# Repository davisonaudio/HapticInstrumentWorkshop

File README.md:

# HaptiCoupler System

This repository contaisn the design files and firmware for the HaptiCoupler system.
It also contains information for the Haptic instrument study that used the HaptiCoupler system to explore digital musical instrument designs.

More information about the system can be found in the Wiki tab of this repo.

The HaptiCoupler is a device that enables simultaneous tactile sensing and haptic feedback through a signle voice coil transducer.

This is achieved by actuating the voice coil with a voltage and sensing with current, along with some DSP running on the Teensy 4.0 to cancel the actuation signal from the sensing signal.

It is designed primarily for use with audio-driven digital resonator instruments, though can be used for other purposes.

# HapticInstrumentWorkshop
Information for the self-sensing vibrotactile haptic instrument design project. Part of the Augmented Instruments Lab at Imperial College London

For more information on using the kit and detailed documentation, visit the [wiki](https://github.com/davisonaudio/HapticInstrumentWorkshop/wiki).

Access the web control panel [here](https://davisonaudio.github.io/HapticInstrumentWorkshop/) for logging information and parameter adjustment.

# Kit Contents

- 1x Teensy 4.0 Microcontroller development board with headers
- 1x custom amplifier PCB (using MAX98789 amplifier)
- 1x Dayton Audio EX32VBDS-4 Voice Coil Transducer
- 1x 9V DC 5.1mm barrel jack power supply (centre-positive)
- 1x USB A to micro USB cable

# Getting Started
The Teensy 4.0 will come preloaded with the required firmware and mounted with its headers onto the top of the amplifier board. 

# Cloning the repo
To get a local copy of this repository (for editing the firmware or hardware files included), run the following command:
> git clone --recurse-submodules https://github.com/davisonaudio/HapticInstrumentWorkshop.git

This will clone the main repo as well as the audio-utils submodule within the firmware folder.

# Hacking the Hardware

It is unlikely that the PCB is something that we be modified as part of this study. For those with sufficient electronics knowledge, however, the design files (schematic and PCB PDFs along with KiCAD files) can be found in the hardware folder of this repo.

# Hacking the Example Software

# Hacking the Firmware
For advanced users, the firmware running on the Teensy can be modified and recompiled. All of the required files are within the firmware folder of this repo.

The firmware is developed for the Teensy using [PlatformIO](https://platformio.org). This provides more flexibility than using the Arduino IDE (as is often used with Teensy and similar boards), but still allows use of the Teensy system's wide array of useful C++ libraries. It also avoids the increased complexities of utilising a proper embedded development environment (such as NXP's MCUXpresso for the Teensy 4.0's NXP RT1060 microcontroller).

Visual Studio Code is required for PlatformIO development. For further details of development environment setup please refer to the wiki.

# Publications
For more information on related research output of this project, please refer to the below publications:

- M. Davison, C. J. Webb, M. Ducceschi and A. P. McPherson. A self-sensing haptic actuator for tactile interaction with physical modelling synthesis. *Proc. International Conference on New Interfaces for Musical Expression (NIME)*, Utrecht, Netherlands. 2024. [PDF](http://instrumentslab.org/data/andrew/davison_nime2024.pdf)

- M. Davison and A. P. McPherson. A self-sensing vibrotactile transducer for bidirectional interaction. *Proc. Eurohaptics* (work in progress), Lille, France. 2024. [PDF](http://instrumentslab.org/data/andrew/davison_eurohaptics2024.pdf)

# Contributors
This project is developed and maintained by Matt Davison. Massive thank you also to the additional contributors who helped this project happen:

- Anna Silver - CAD design of 3D printed elements
- David Gong - Initial PCB design and firmware bring-up of the amplifier board
- Prof. Andrew McPherson - Supervision and guidance throughout

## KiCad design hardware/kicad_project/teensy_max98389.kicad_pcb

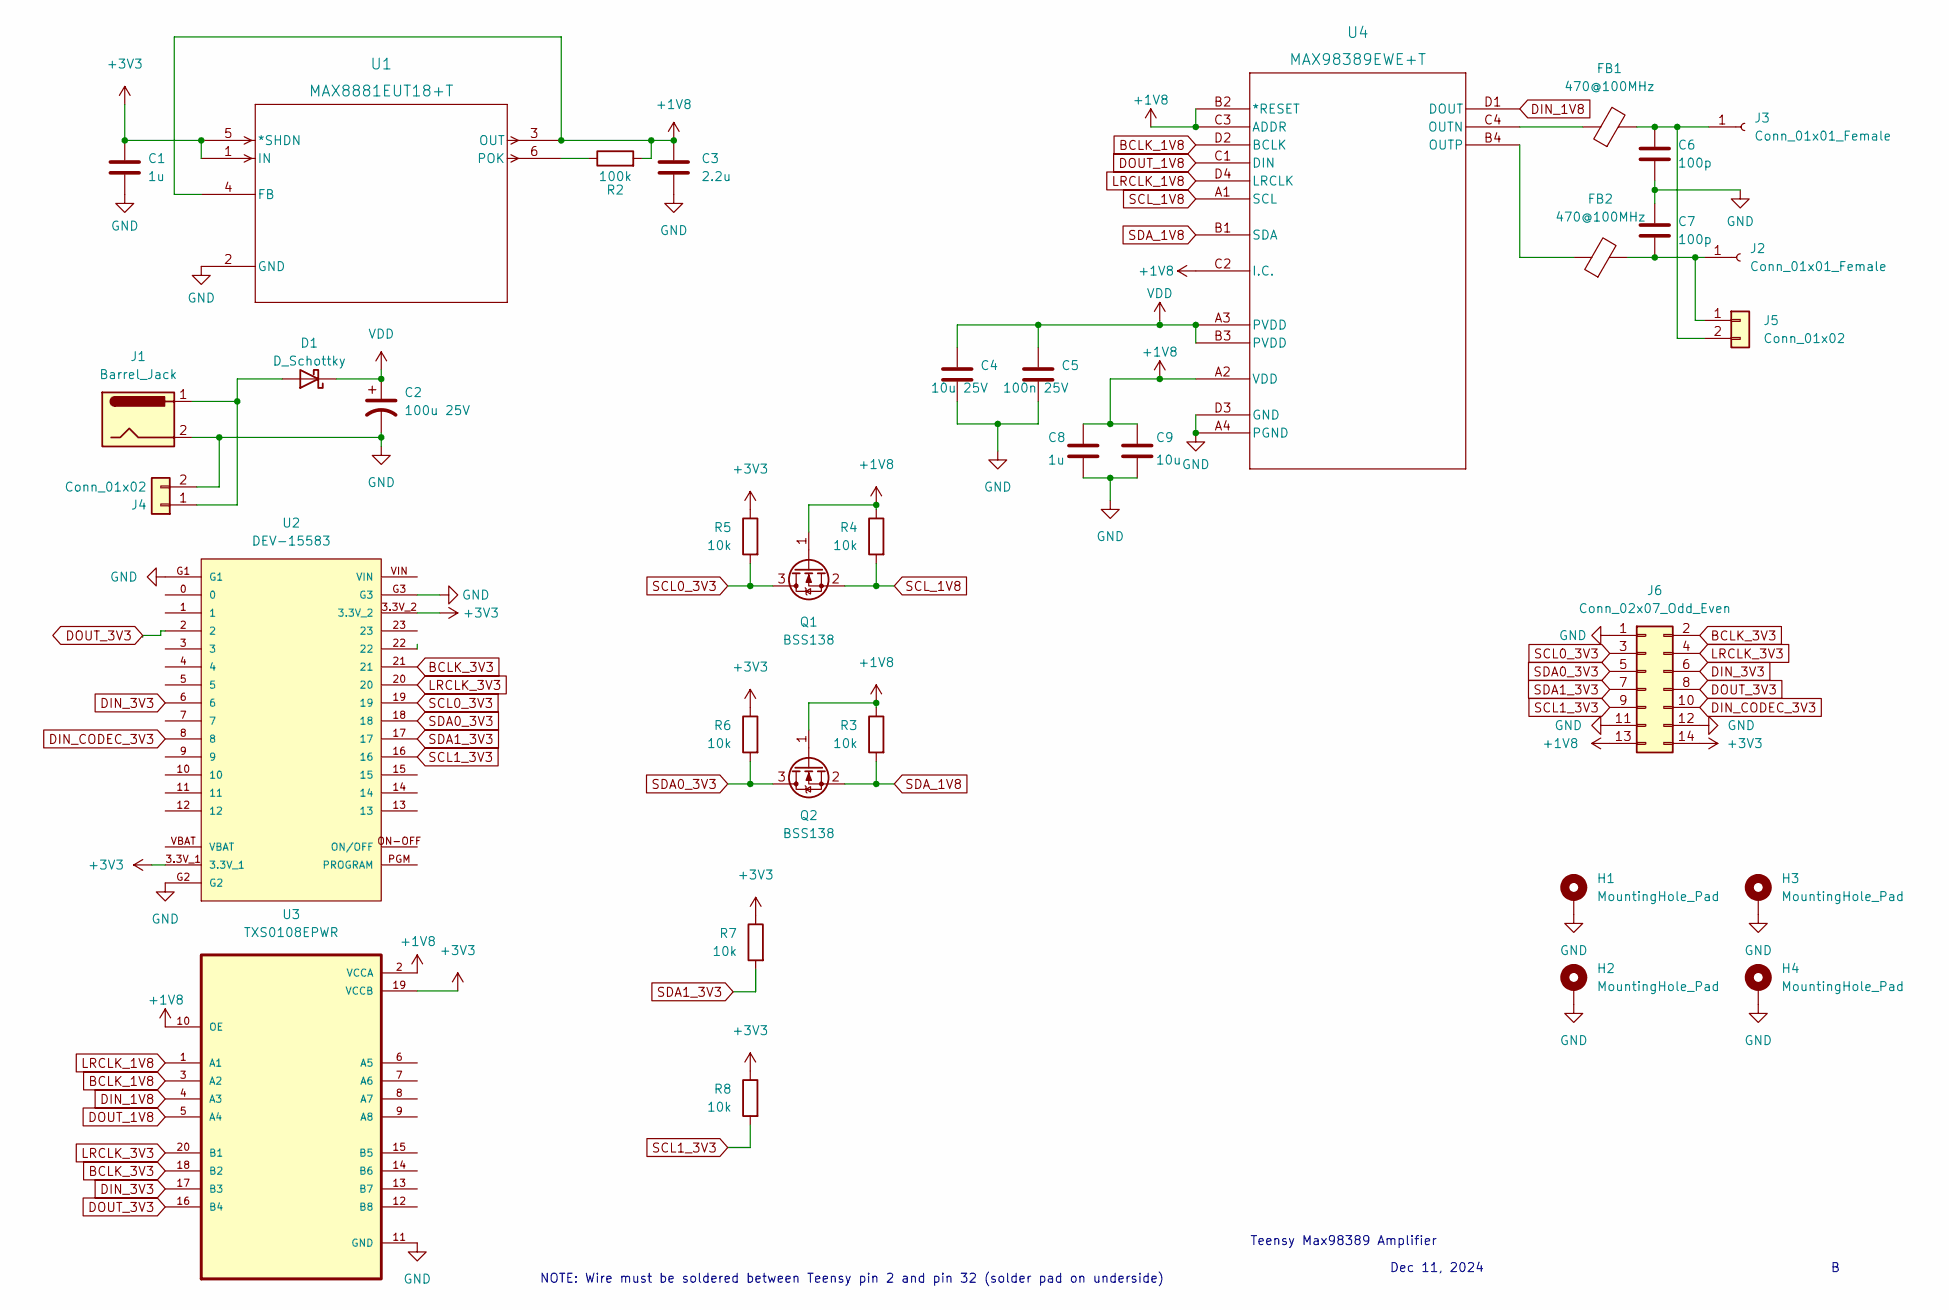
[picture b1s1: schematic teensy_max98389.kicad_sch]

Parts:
C1, C8: 1u; C_0603_1608Metric
C2: 100u 25V; CP_Radial_D6.3mm_P2.50mm
C3: 2.2u; C_0603_1608Metric
C4: 10u 25V; C_0603_1608Metric
C5: 100n 25V; C_0603_1608Metric
C6, C7: 100p; C_0603_1608Metric
C9: 10u; C_0603_1608Metric
D1: D_Schottky; D_0603_1608Metric
FB1, FB2: 470@100MHz; L_0805_2012Metric
H1, H2, H3, H4: MountingHole_Pad; MountingHole_3.2mm_M3_DIN965_Pad_TopBottom
J1: Barrel_Jack; BarrelJack_Kycon_KLDX-0202-xC_Horizontal
J2, J3: Conn_01x01_Female; MountingHole_6.4mm_M6_DIN965_Pad
J4, J5: Conn_01x02; Molex_KK-254_AE-6410-02A_1x02_P2.54mm_Vertical
J6: Conn_02x07_Odd_Even; PinHeader_2x07_P2.54mm_Vertical
Q1, Q2: BSS138; SOT-23
R2: 100k; R_0603_1608Metric
R3, R4, R5, R6, R7, R8: 10k; R_0603_1608Metric
U1: MAX8881EUT18+T; 21-0058I_MXM
U2: DEV-15583; MODULE_DEV-15583
U3: TXS0108EPWR; SOP65P640X120-20N
U4: MAX98389EWE+T; 21-100636_ADI

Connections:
+1V8: C3.1, C8.1, C9.1, J6.13, Q1.1 (G), Q2.1 (G), R2.2, R3.1, R4.1, U1.3 (OUT), U1.4 (FB), U3.2 (VCCA), U3.10 (OE), U4.A2 (VDD), U4.B2 (*RESET), U4.C2 (I.C.), U4.C3 (ADDR)
+3V3: C1.1, J6.14, R5.1, R6.1, R7.1, R8.1, U1.1 (IN), U1.5 (*SHDN), U2.3.3V_1, U2.3.3V_2, U3.19 (VCCB)
BCLK_1V8: U3.3 (A2), U4.D2 (BCLK)
BCLK_3V3: J6.2, U2.21, U3.18 (B2)
DIN_1V8: U3.4 (A3), U4.D1 (DOUT)
DIN_3V3: J6.6, U2.6, U3.17 (B3)
DIN_CODEC_3V3: J6.10, U2.8
DOUT_1V8: U3.5 (A4), U4.C1 (DIN)
DOUT_3V3: J6.8, U2.2, U3.16 (B4)
GND: C1.2, C2.2, C3.2, C4.2, C5.2, C6.2, C7.1, C8.2, C9.2, H1.1, H2.1, H3.1, H4.1, J1.2, J4.2, J6.1, J6.11, J6.12, U1.2 (GND), U2.G1, U2.G2, U2.G3, U3.11 (GND), U4.A4 (PGND), U4.D3 (GND)
LRCLK_1V8: U3.1 (A1), U4.D4 (LRCLK)
LRCLK_3V3: J6.4, U2.20, U3.20 (B1)
unnamed: D1.2 (A), J1.1, J4.1
unnamed: C7.2, FB2.2, J2.1, J5.1
unnamed: C6.1, FB1.2, J3.1, J5.2
unnamed: R2.1, U1.6 (POK)
unnamed: FB1.1, U4.C4 (OUTN)
unnamed: FB2.1, U4.B4 (OUTP)
SCL0_3V3: J6.3, Q1.3 (D), R5.2, U2.19
SCL1_3V3: J6.9, R8.2, U2.16
SCL_1V8: Q1.2 (S), R4.2, U4.A1 (SCL)
SDA0_3V3: J6.5, Q2.3 (D), R6.2, U2.18
SDA1_3V3: J6.7, R7.2, U2.17
SDA_1V8: Q2.2 (S), R3.2, U4.B1 (SDA)
VDD: C2.1, C4.1, C5.1, D1.1 (K), U4.A3 (PVDD), U4.B3 (PVDD)

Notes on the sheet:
Dec 11, 2024
NOTE: Wire must be soldered between Teensy pin 2 and pin 32 (solder pad on underside)
Teensy Max98389 Amplifier

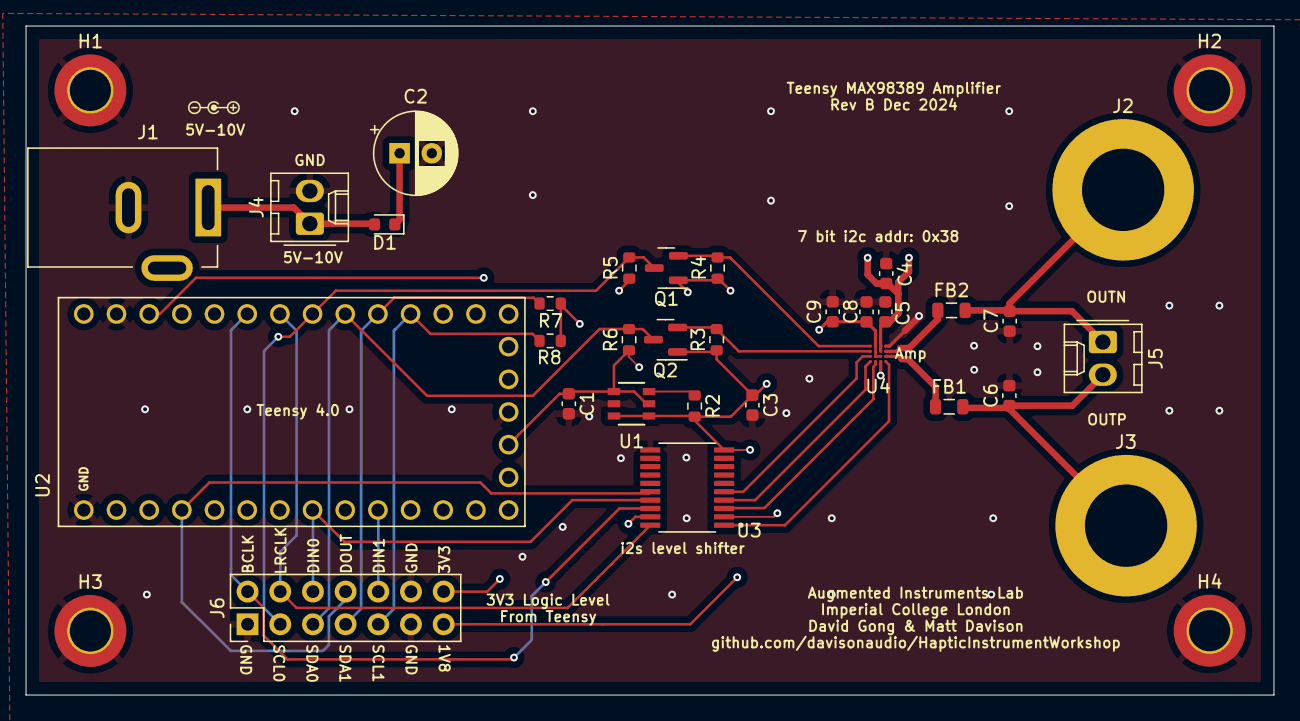
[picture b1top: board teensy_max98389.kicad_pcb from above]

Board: 4 copper layers, 97.0 x 52.0 mm, 35 parts (0 on the bottom side), 25 nets.

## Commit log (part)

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2024-10-11 Added datasheets
2024-10-29 Added firmware, safety doc, schematic pdf
2024-10-29 Added audio utils
2024-11-01 Added documentation
2024-11-04 Added gitignore to root of repo
2024-11-04 Fixed firmware build error with audio utils
2024-11-14 Removed firmware compiled units
2024-11-14 Added .pio to gitignore, MidiComms and EEPROM placeholder files
2024-11-17 FIRMWARE: Implemented EEPROM read/write class
2024-11-21 FIRMWARE: Added volume control
2024-11-29 FIRMWARE: Changes for CHIME demo day (in progress)
2024-12-01 FIRMWARE: Added force sense debug print option
2024-12-01 FIRMWARE: Goertzel setup
2024-12-14 FIRMWARE: Work to get force sensing working (in progress)
2025-01-14 Added debug messages to serial on boot
2025-01-27 Added debug options
2025-01-28 Added 3D printing files
2025-01-29 Initial rev b bringup changes
2025-01-31 Rev B bringup, added MIDI rx boilerplate and EEPROM serial number storage
2025-01-31 Added p5.js control panel site
2025-01-31 Create static.yml for deploying GitHub pages
2025-02-02 Added template functions to convert to/from int and normalised float
2025-02-03 Cleaned up main.cpp, added conversion to/from float and int16
2025-02-03 Implemented EEPROM read
2025-02-03 FIRMWARE: Added midi control of calibration, resonant freq and eeprom write
2025-02-03 WEBSITE: Added basic USB midi control
2025-02-05 Website development - control sliders
2025-02-08 Changed website js layout, fixed normalisedToInt bug in audio-utils
2025-02-08 Changes to still output to amplifier when USB audio not running
2025-02-08 Added MIDI command to reset parameters to compiled defaults in firmware.
2025-02-09 Added send serial details function
2025-02-09 Implemented control of resonant frequency via pitch bend channel 0
2025-02-09 Implemented MIDI output of force sensing value
2025-02-09 UPVERSION: V1.0 Initial Release
2025-02-13 Updated actuator base STL file
2025-02-19 Added gain reducation at resonance to improve force sense
2025-02-19 Added smoothing filter for force sensing values, added storing and recalling force sense calibration in EEPROM, added resonant filter for actuation signal
2025-02-25 Added rxControlChange
2025-02-25 FIRMWARE: Reorganised EEPROM addresses for compatibility. WARNING: Breaks compatibility with previous firmware version's EEPROM address layout
2025-03-03 Added debug/release build option
2025-03-06 Added rev B schematic
2025-03-06 Added new screwtop CAD file
2025-03-07 Added board revision to EEPROM - not yet used
2025-03-07 UPVERSION: V1.1 - Storage version number and refactor of EEPROM ordering, MIDI control of tone level
2025-03-07 Firmware and website: Added serial input textbox to website and began implementation of serial control of parameters
2025-03-07 Minor fix to prevent text labels scrolling with logging o nwebsite
2025-03-10 Implemented serial control of resonant q, resonant gain, wideband gain, and reading of current values
2025-03-10 Refactored serial commands into separate file
2025-03-10 Added additional serial controls and serial command help message
2025-03-10 Added calibrate damped/undamped serial commands and recall last input on serial website interface
2025-03-10 Added info serial command
2025-03-10 UPVERSION: V1.2
2025-03-13 Added control of input and output lowpass cutoff frequencies
2025-03-13 UPVERSION: V1.3
2025-03-26 UPVERSION: V1.4 - Added reading of LPF values from EEPROM
2025-03-27 Added help text to interface and option to press enter to send commands
2025-05-21 Fixed text on serial monitor
2025-06-02 Initial audio board development
2025-06-13 Added standalone karplus strong synth, inidividual control of headphone and actuation levels, more audio routing options
2025-06-19 Moved audio code to own AudioRouter file, added initial development for interfacing with the control board
2025-06-25 Fixed erors to make refactored audio work, added audio shield mode to eeprom, added code to test i2c control board
2025-07-09 Added option for analogue mode (audio shield used instead of USB) - WARNING: this uses 8 sample buffer size
2025-07-09 Added setting of max buffers for audio queues
2025-07-22 Added faust bell physical model
2025-08-02 Update audio-utils submodules
2025-11-14 Altered to use resonant frequencies that have period equal to integer number of sample
2025-12-22 Added Kicad project
2025-12-27 Changed sample rate register setting to sense currrent from 10kHz to 20kHz
2026-02-17 audio-utils update
2026-02-19 Changed audio routing to use custom teensy audio object instead of queues and added audio loopback test
2026-02-25 Fix for voltage and current being wrong way around, added piezo mode (passthrough to USB)
2026-02-26 Added run-time recall of PCB revision and appropriate audio routing
2026-02-26 Added MIDI control of output levels and karplus synth
2026-03-13 Added faust bell physical model (not working)
2026-03-18 Initial code to set inductance filtering
2026-05-02 Added storing and retrieving of inductance coefficients to/from eeprom
2026-05-03 Added function descriptions
2026-05-03 added adc input for accelerometer measurements
2026-05-03 added set mode serial command
